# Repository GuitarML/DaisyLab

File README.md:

# DaisyLab

This project is a work in progress and accompanies this [Youtube Video](https://youtu.be/a7t4HOnyYJc?si=x94Irn_ftIJcWl1D) for transforming a midi controller into a standalone instrument.

Includes KiCad hardware pcb and Gerbers, along with firmware for running synthesizers.

Currently requires modifying the daisy_petal.cpp and .h files before building libdaisy (modified files included in software/mod).

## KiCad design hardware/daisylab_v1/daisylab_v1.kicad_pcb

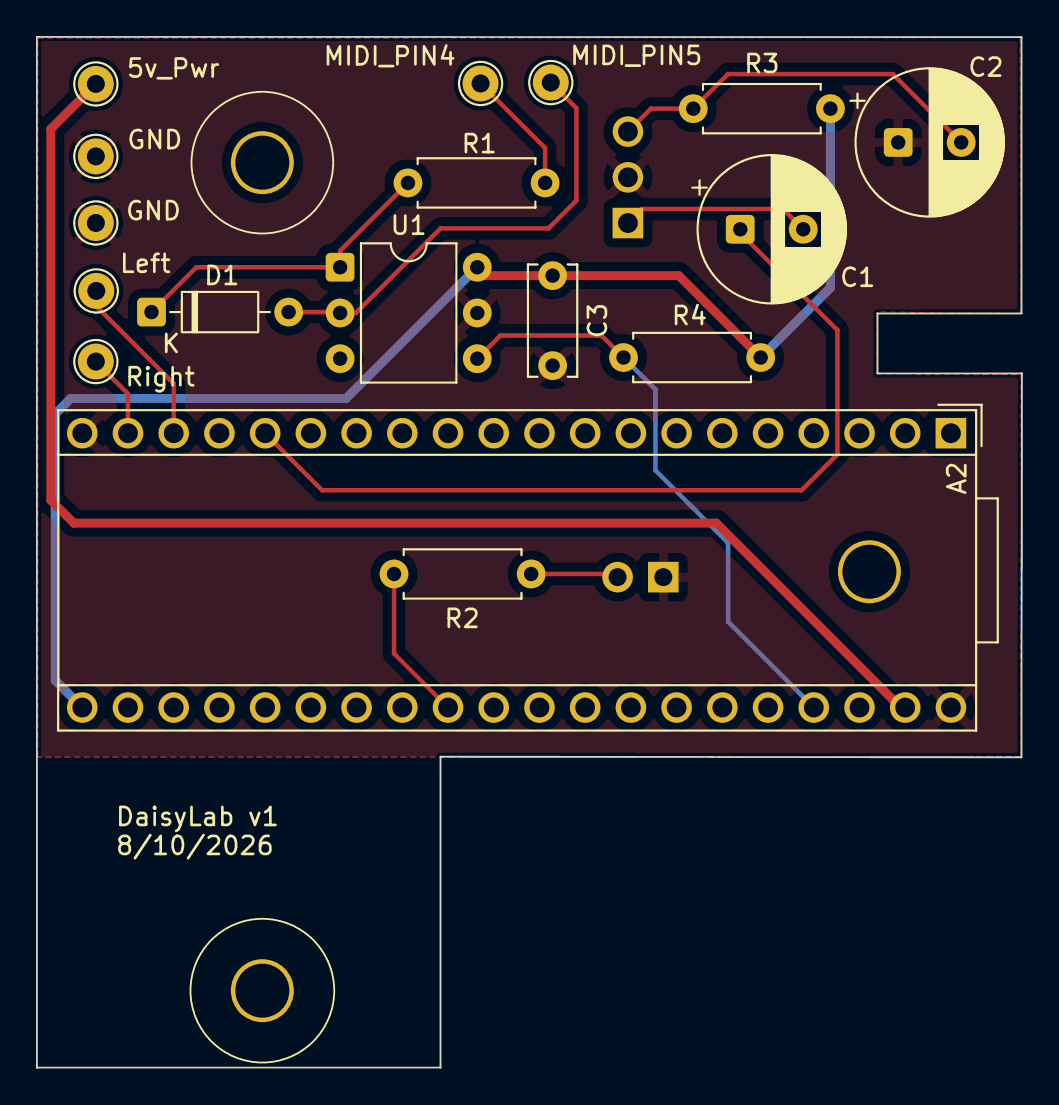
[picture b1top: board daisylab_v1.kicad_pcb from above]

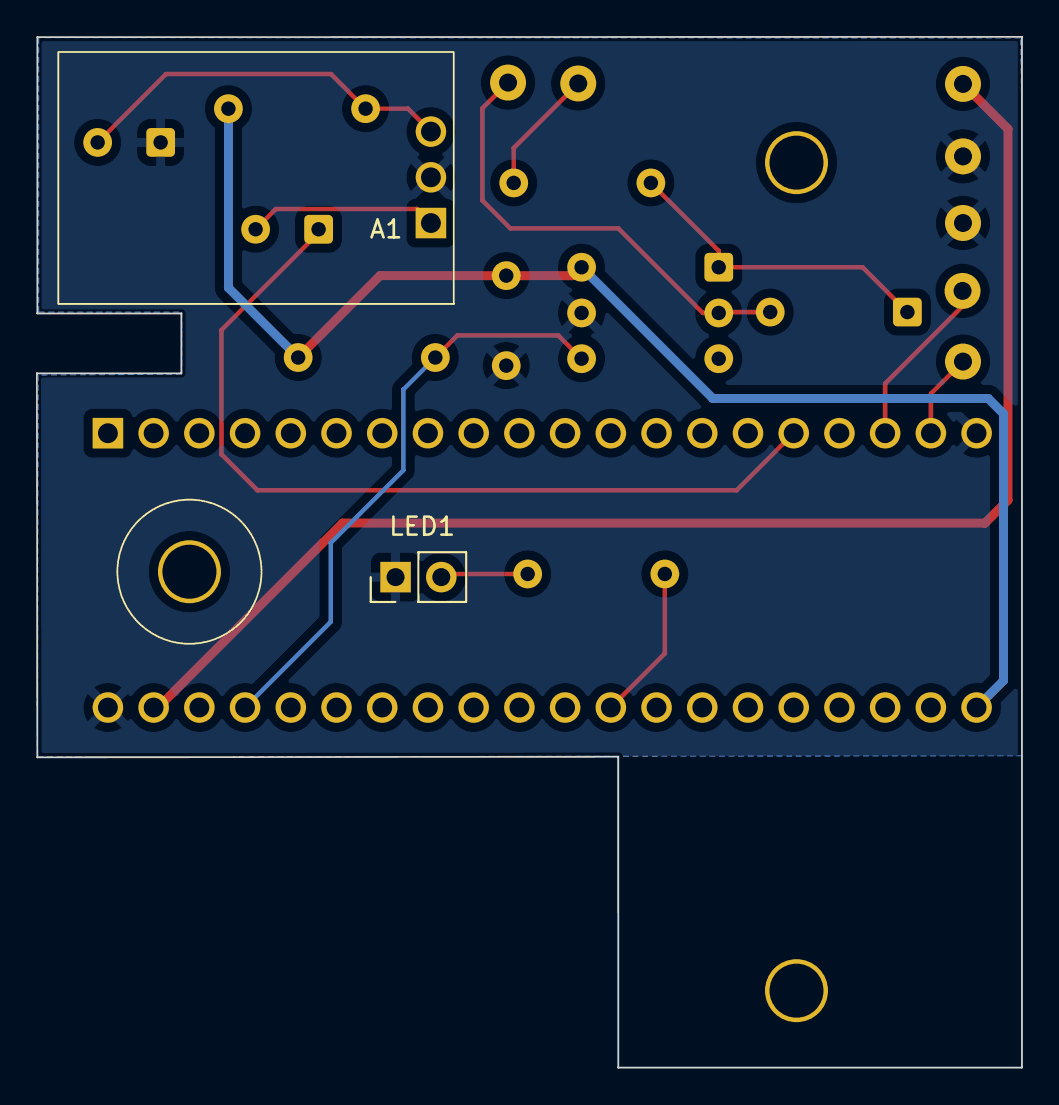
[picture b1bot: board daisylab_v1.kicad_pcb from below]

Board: 2 copper layers, 54.7 x 57.3 mm, 20 parts (2 on the bottom side), 14 nets.

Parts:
5v_Pwr: TestPoint_THTPad_D2.0mm_Drill1.0mm
A1: Adafruit MAX4466 Breakout; Adafruit_MAX4466
A2: Electrosmith_Daisy_Seed_Rev7; Electrosmith_Daisy_Seed
C1, C2: 100UF; CP_Radial_D8.0mm_P3.50mm
C3: 100NF; C_Disc_D6.0mm_W2.5mm_P5.00mm
D1: 1N4148; D_DO-35_SOD27_P7.62mm_Horizontal
GND: TestPoint_THTPad_D2.0mm_Drill1.0mm
GND#2: TestPoint_THTPad_D2.0mm_Drill1.0mm
LED1: LED_1; PinHeader_1x02_P2.54mm_Vertical
Left: TestPoint_THTPad_D2.0mm_Drill1.0mm
MIDI_PIN4, MIDI_PIN5: TestPoint_THTPad_D2.0mm_Drill1.0mm
Mount: MountingHole_3mm
R1: 220R; R_Axial_DIN0207_L6.3mm_D2.5mm_P7.62mm_Horizontal
R2: 1K; R_Axial_DIN0207_L6.3mm_D2.5mm_P7.62mm_Horizontal
R3: 100R; R_Axial_DIN0207_L6.3mm_D2.5mm_P7.62mm_Horizontal
R4: 470R; R_Axial_DIN0207_L6.3mm_D2.5mm_P7.62mm_Horizontal
Right: TestPoint_THTPad_D2.0mm_Drill1.0mm
U1: H11L1; DIP-6_W7.62mm

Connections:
3V3_A: A2.21 (3V3_A), C3.1, R3.1, R4.1, U1.6
AUDIO_IN_LEFT_DAISY: A2.16 (AUDIO_IN_1), C1.1
AUDIO_OUT_BUFFER_LEFT: A2.18 (AUDIO_OUT_1), Left.1
AUDIO_OUT_BUFFER_RIGHT: A2.19 (AUDIO_OUT_2), Right.1
GND: A1.2 (GND), A2.20 (AGND), A2.40 (DGND), C2.1, C3.2, GND.1, GND#2.1, LED1.1 (K), U1.5
LED_1: A2.29 (DAC_OUT2), R2.2
MIDI_IN: A2.37 (USB_D_+), R4.2, U1.4
MIDI_IN_JACK_PIN4: MIDI_PIN4.1, R1.1
MIDI_IN_JACK_PIN5: D1.2 (A), MIDI_PIN5.1, U1.2
unnamed: 5v_Pwr.1, A2.39 (VIN)
unnamed: A1.1 (OUT), C1.2
unnamed: A1.3 (VCC), C2.2, R3.2
unnamed: D1.1 (K), R1.2, U1.1
unnamed: LED1.2 (A), R2.1
